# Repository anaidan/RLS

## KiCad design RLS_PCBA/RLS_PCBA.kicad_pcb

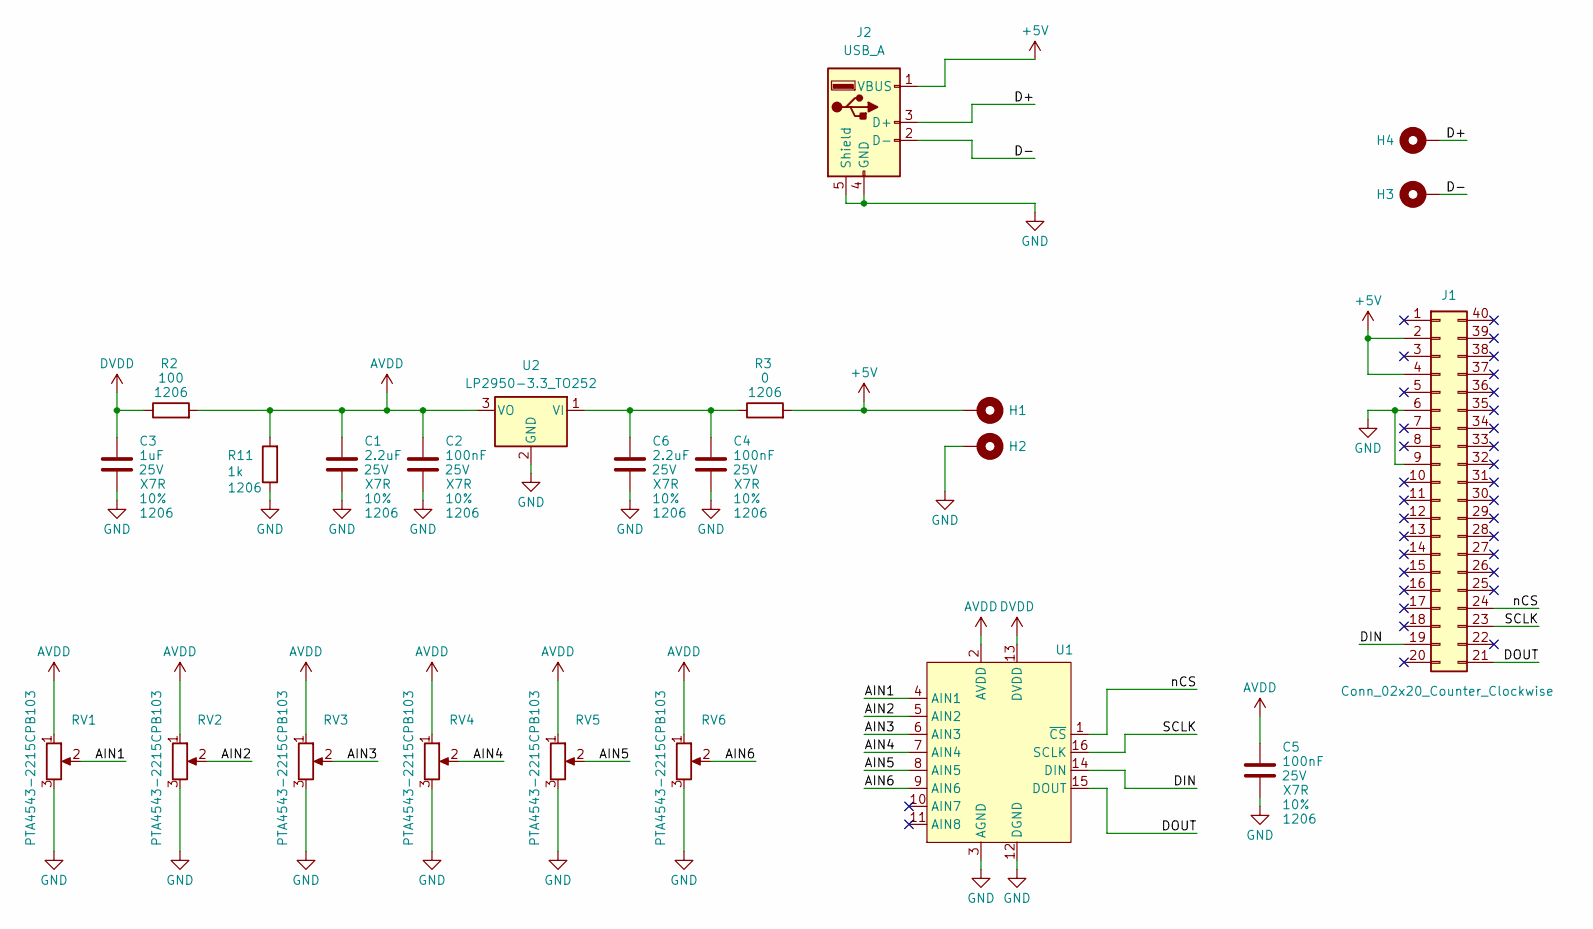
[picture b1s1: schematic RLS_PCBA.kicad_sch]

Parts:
C1, C6: 2.2uF; C_1206_3216Metric; Voltage Rating 25V; Tolerance 10%
C2, C4, C5: 100nF; C_1206_3216Metric; Voltage Rating 25V; Tolerance 10%
C3: 1uF; C_1206_3216Metric; Voltage Rating 25V; Tolerance 10%
H1, H2: MountingHole_Pad; MountingHole_2.2mm_M2_Pad_TopOnly
H3, H4: MountingHole_Pad; MountingHole_2.2mm_M2_DIN965_Pad_TopOnly
J1: Conn_02x20_Counter_Clockwise; Connector_PinHeader_2.54mmPinHeader_2x20_P2.54mm_Vertical_S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
J2: USB_A; CONN_73725-0110BLF_AMP
R2: 100; R_1206_3216Metric
R3: 0; R_1206_3216Metric
R11: 1k; R_1206_3216Metric
RV1, RV2, RV3, RV4, RV5, RV6: PTA4543-2215CPB103; PTA1543-2
U1: TSSOP-16_4.4x5mm_P0.65mm
U2: LP2950-3.3_TO252; TO-252-2

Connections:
+5V: H1.1, J1.2, J1.4, J2.1 (VBUS), R3.2
/AIN1: RV1.2, U1.4 (AIN1)
/AIN2: RV2.2, U1.5 (AIN2)
/AIN3: RV3.2, U1.6 (AIN3)
/AIN4: RV4.2, U1.7 (AIN4)
/AIN5: RV5.2, U1.8 (AIN5)
/AIN6: RV6.2, U1.9 (AIN6)
/D+: H4.1, J2.3 (D+)
/D-: H3.1, J2.2 (D-)
/DIN: J1.19, U1.14 (DIN)
/DOUT: J1.21, U1.15 (DOUT)
/SCLK: J1.23, U1.16 (SCLK)
/nCS: J1.24, U1.1 (~CS)
AVDD: C1.1, C2.1, C5.1, R2.2, R11.2, RV1.1, RV2.1, RV3.1, RV4.1, RV5.1, RV6.1, U1.2 (AVDD), U2.3 (VO)
DVDD: C3.1, R2.1, U1.13 (DVDD)
GND: C1.2, C2.2, C3.2, C4.2, C5.2, C6.2, H2.1, J1.6, J1.9, J2.4 (GND), J2.5 (Shield), R11.1, RV1.3, RV2.3, RV3.3, RV4.3, RV5.3, RV6.3, U1.3 (AGND), U1.12 (DGND), U2.2 (GND)
unnamed: C4.1, C6.1, R3.1, U2.1 (VI)

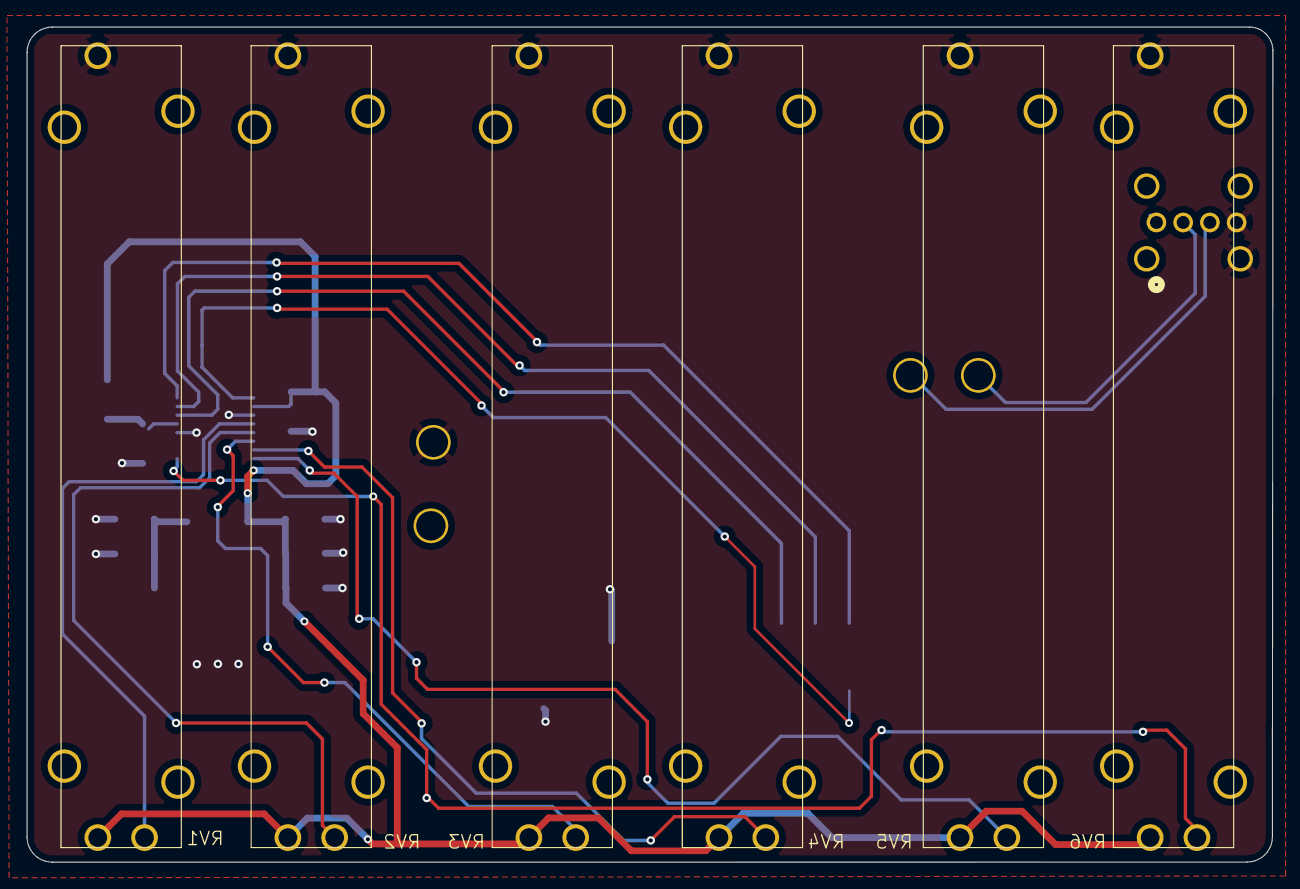
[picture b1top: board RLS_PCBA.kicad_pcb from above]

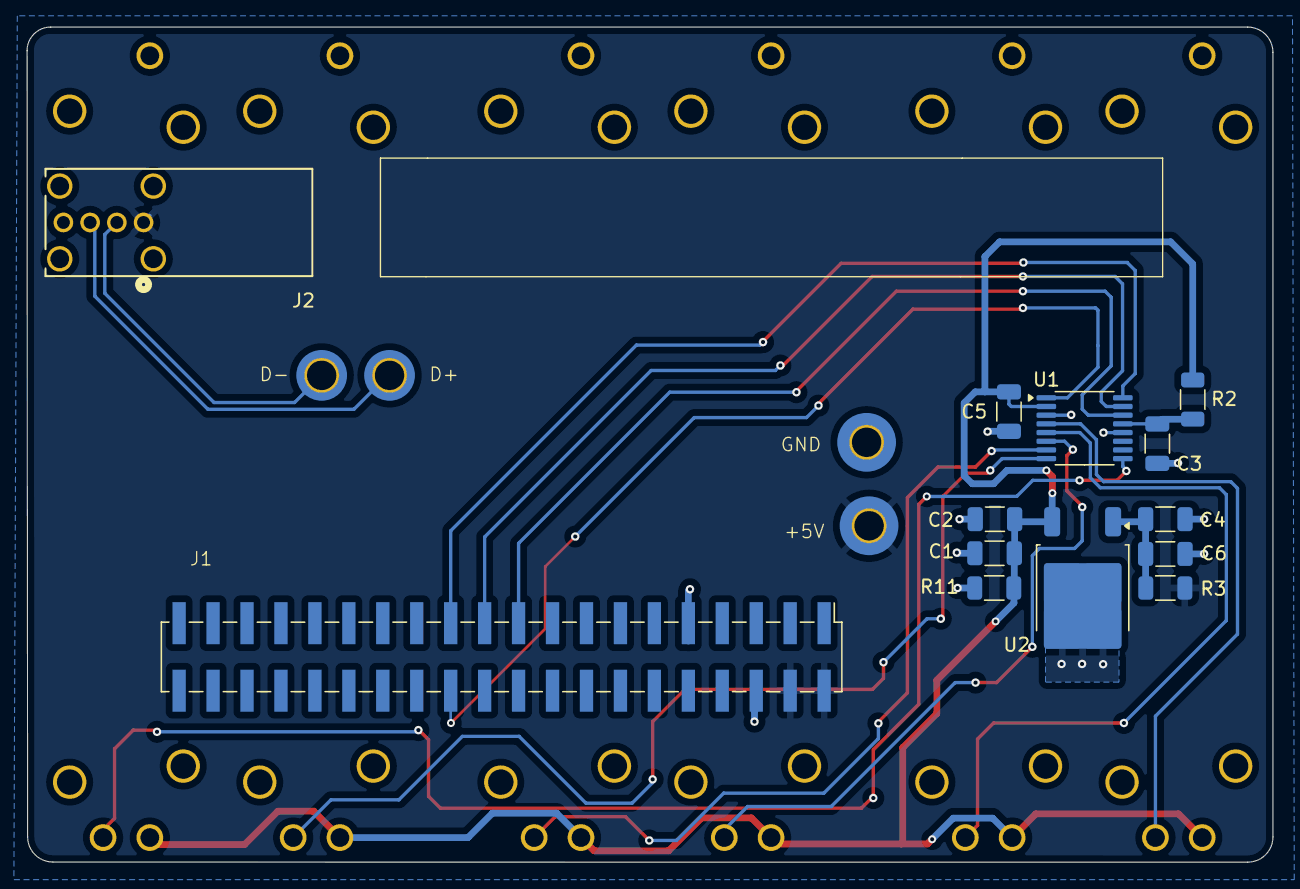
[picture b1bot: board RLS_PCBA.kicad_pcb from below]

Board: 2 copper layers, 93.2 x 62.5 mm, 23 parts (17 on the bottom side), 17 nets.

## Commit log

2024-10-04 added ignore
2024-10-04 Hardware files
